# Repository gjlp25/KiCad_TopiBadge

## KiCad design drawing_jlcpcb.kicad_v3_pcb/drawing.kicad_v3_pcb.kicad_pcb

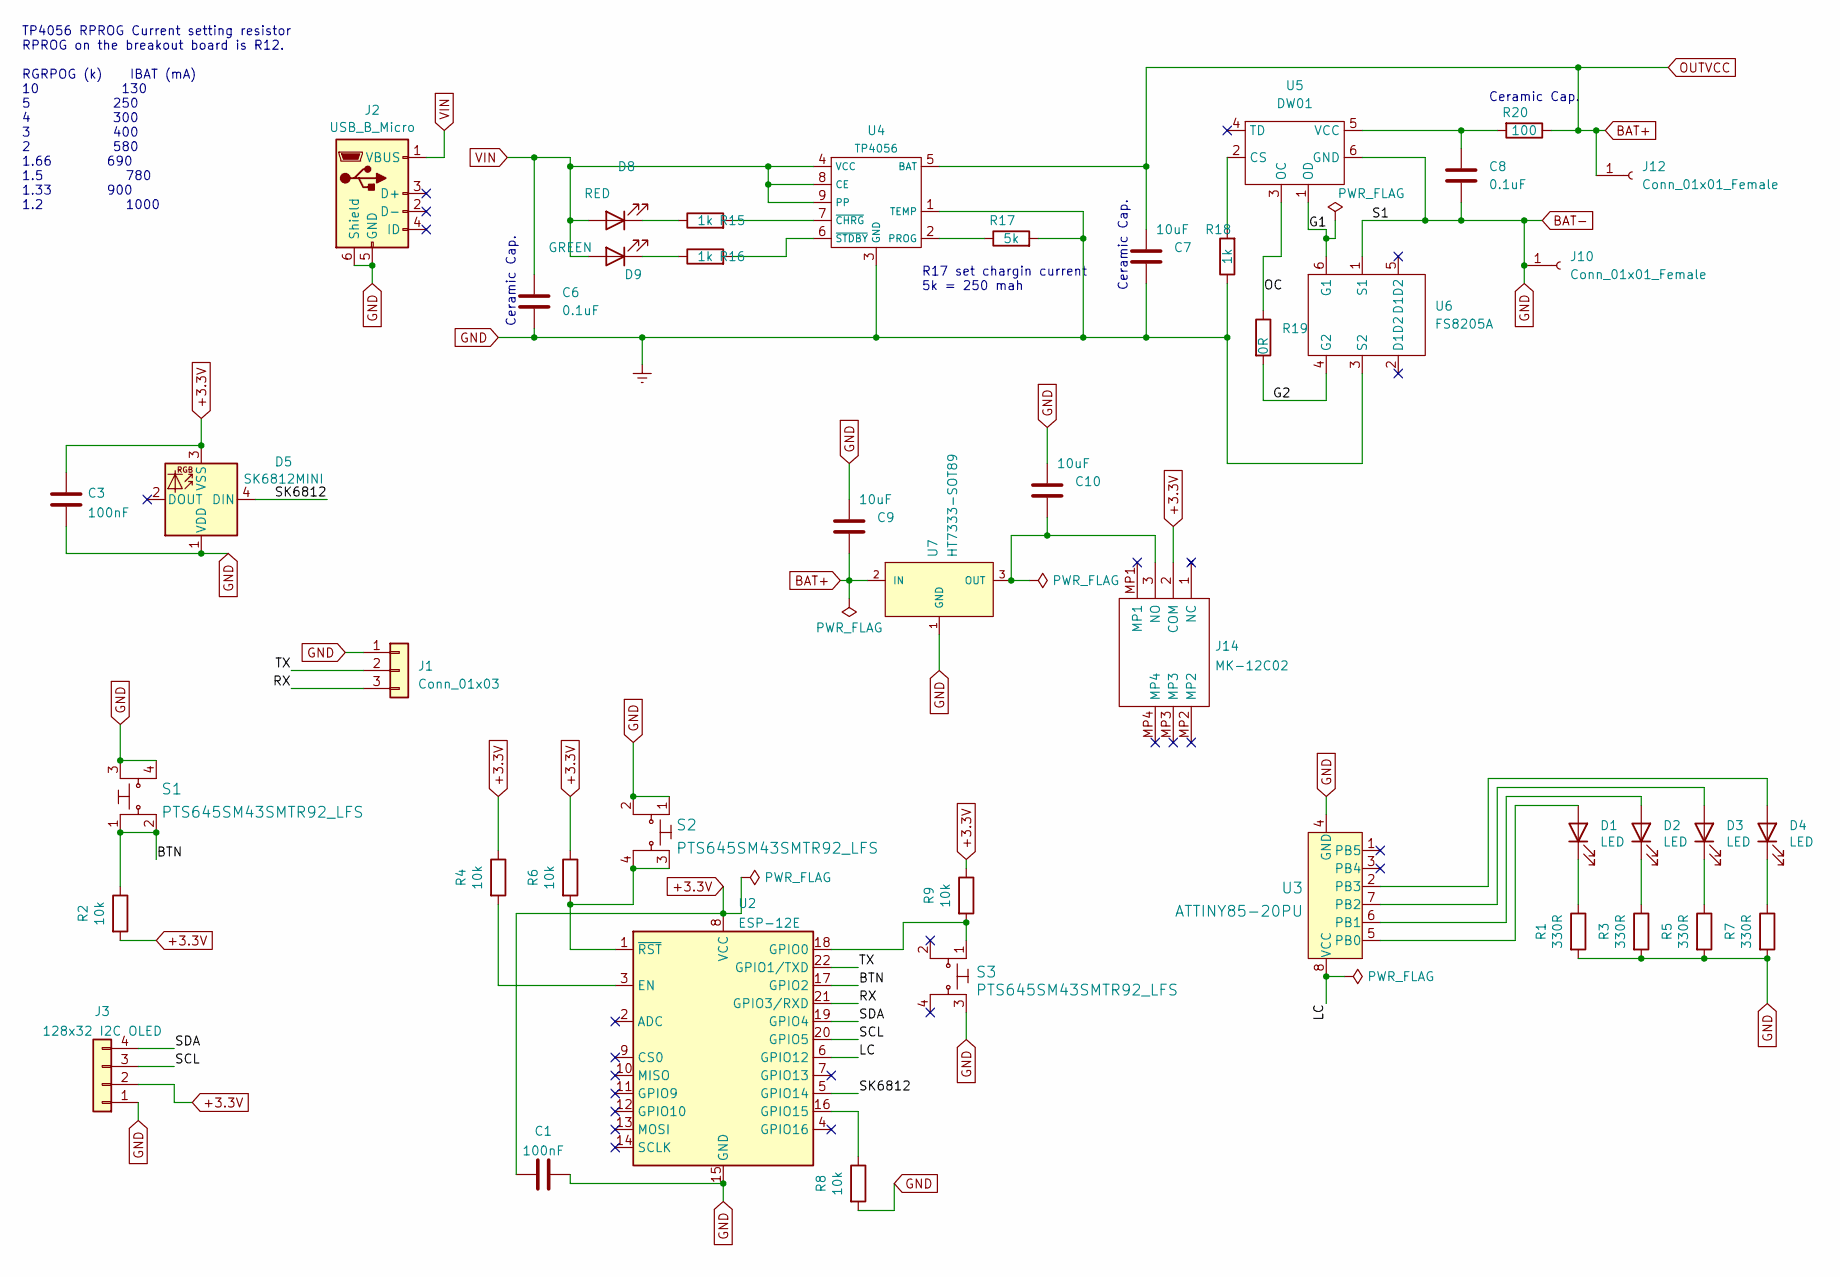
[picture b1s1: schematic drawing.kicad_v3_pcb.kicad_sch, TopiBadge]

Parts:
C1, C3: 100nF; C_0805_2012Metric_Pad1.18x1.45mm_HandSolder
C6, C8: 0.1uF; C_0805_2012Metric_Pad1.18x1.45mm_HandSolder
C7, C9, C10: 10uF; C_0805_2012Metric_Pad1.18x1.45mm_HandSolder
D1, D2, D3, D4: LED; LED_0805_2012Metric_Pad1.15x1.40mm_HandSolder
D5: SK6812MINI; LED_SK6812MINI_PLCC4_3.5x3.5mm_P1.75mm
D8: RED; LED_0805_2012Metric_Pad1.15x1.40mm_HandSolder
D9: GREEN; LED_0805_2012Metric_Pad1.15x1.40mm_HandSolder
J1: Conn_01x03; PinSocket_1x03_P2.54mm_Horizontal
J2: USB_B_Micro; USB_Micro_B_Female_10118194-0001LF
J3: 128x32 I2C OLED; PinSocket_1x04_P2.54mm_Vertical
J10, J12: Conn_01x01_Female; solderpad
J14: MK-12C02; MK12C02; Manufacturer_Part_Number MK-12C02
R1, R3, R5, R7: 330R; R_0805_2012Metric_Pad1.20x1.40mm_HandSolder
R2, R4, R6, R8, R9: 10k; R_0805_2012Metric_Pad1.20x1.40mm_HandSolder
R15, R16, R18: 1k; R_0603_1608Metric_Pad0.98x0.95mm_HandSolder
R17: 5k; R_0805_2012Metric_Pad1.20x1.40mm_HandSolder
R19: 0R; R_1206_3216Metric_Pad1.30x1.75mm_HandSolder
R20: 100; R_0805_2012Metric_Pad1.20x1.40mm_HandSolder
S1, S2, S3: PTS645SM43SMTR92_LFS; Switch_Tactile_SMD_6x6mm_PTS645; MPN PTS645SM43SMTR92 LFS; Digi-Key_PN CKN9112CT-ND
U2: ESP-12E
U3: ATTINY85-20PU; SMDIP-8_W7.62mm; MPN ATTINY85-20PU; Digi-Key_PN ATTINY85-20PU-ND
U4: TP4056; SOIC-8-1EP_3.9x4.9mm_P1.27mm_EP2.29x3mm
U5: DW01; SOT-23-6_Handsoldering
U6: FS8205A; SOT-23-6_Handsoldering
U7: HT7333-SOT89; Holtek-HT7333-SOT89-Level_A

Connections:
+3.3V: C1.1, C3.2, D5.3 (VSS), J3.2, J14.2 (COM), R2.2, R4.1, R6.1, R9.1, U2.8 (VCC)
/BTN: R2.1, S1.1, S1.2, U2.17 (GPIO2)
/G1: U5.1 (OD), U6.6 (G1)
/G2: R19.2, U6.4 (G2)
/LC: U2.6 (GPIO12), U3.8 (VCC)
/OC: R19.1, U5.3 (OC)
/RX: J1.3, U2.21 (GPIO3/RXD)
/SCL: J3.3, U2.20 (GPIO5)
/SDA: J3.4, U2.19 (GPIO4)
/SK6812: D5.4 (DIN), U2.5 (GPIO14)
/TX: J1.2, U2.22 (GPIO1/TXD)
BAT+: C7.1, C9.2, J12.1, R20.1, U4.5 (BAT), U7.2 (IN)
BAT-: C1.2, C3.1, C6.2, C7.2, C8.2, C9.1, C10.1, D5.1 (VDD), J1.1, J2.5 (GND), J2.6 (Shield), J3.1, J10.1, R1.2, R3.2, R5.2, R7.2, R8.2, R17.2, R18.1, S1.3, S1.4, S2.1, S2.2, S3.3, U2.15 (GND), U3.4 (GND), U4.1 (TEMP), U4.3 (GND), U5.6 (GND), U6.1 (S1), U6.3 (S2), U7.1 (GND)
unnamed: D1.2 (A), U3.5 (PB0)
unnamed: D1.1 (K), R1.1
unnamed: D2.2 (A), U3.6 (PB1)
unnamed: D2.1 (K), R3.1
unnamed: D3.2 (A), U3.7 (PB2)
unnamed: D3.1 (K), R5.1
unnamed: D4.2 (A), U3.2 (PB3)
unnamed: D4.1 (K), R7.1
unnamed: D8.1 (K), R15.1
unnamed: D9.1 (K), R16.1
unnamed: C10.2, J14.3 (NO), U7.3 (OUT)
unnamed: R4.2, U2.3 (EN)
unnamed: R9.2, S3.1, U2.18 (GPIO0)
unnamed: R8.1, U2.16 (GPIO15)
unnamed: R6.2, S2.3, S2.4, U2.1 (~RST)
unnamed: R17.1, U4.2 (PROG)
unnamed: R15.2, U4.7 (~CHRG)
unnamed: R16.2, U4.6 (~STDBY)
unnamed: R18.2, U5.2 (CS)
unnamed: C8.1, R20.2, U5.5 (VCC)
VIN: C6.1, D8.2 (A), D9.2 (A), J2.1 (VBUS), U4.4 (VCC), U4.8 (CE), U4.9 (PP)

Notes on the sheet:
Ceramic Cap.
TP4056 RPROG Current setting resistor RPROG on the breakout board is R12. RGRPOG (k) IBAT (mA) 10 130 5 250 4 300 3 400 2 580 1.66 690 1.5 780 1.33 900 1.2 1000
R17 set chargin current 5k = 250 mah

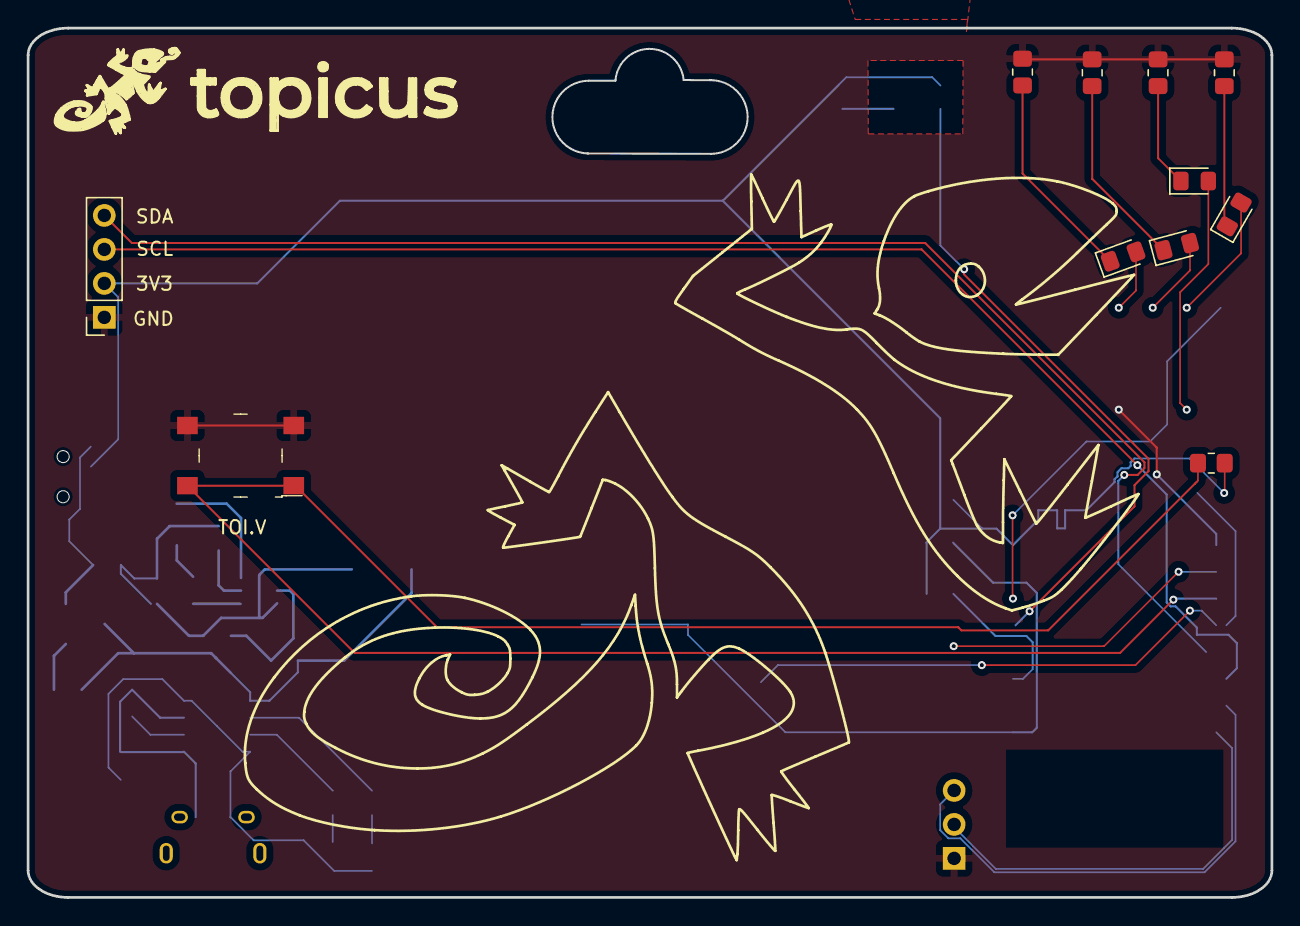
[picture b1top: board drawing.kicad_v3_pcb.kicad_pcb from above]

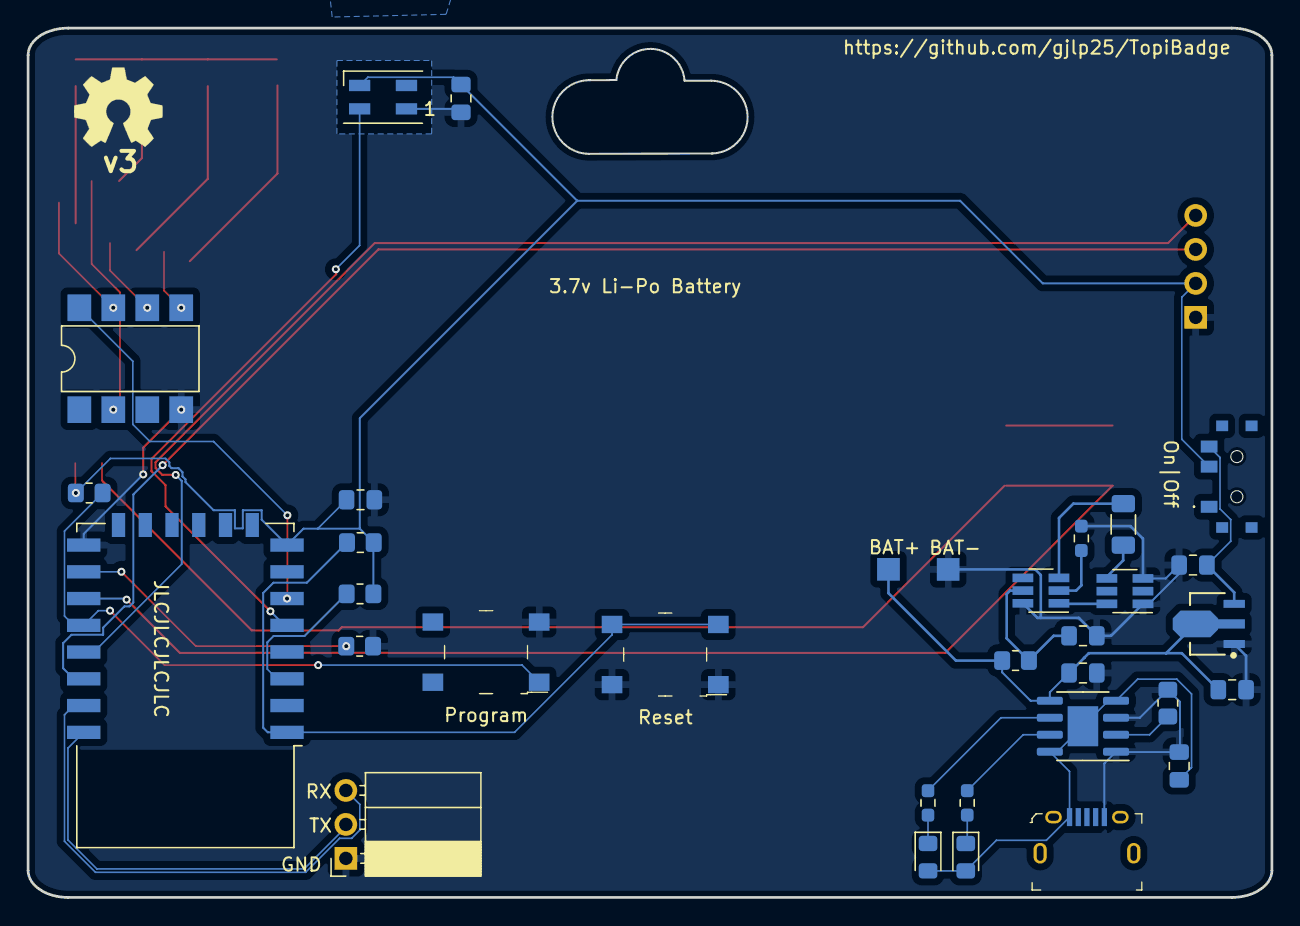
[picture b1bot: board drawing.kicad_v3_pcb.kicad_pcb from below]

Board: 4 copper layers, 93.0 x 65.0 mm, 44 parts (33 on the bottom side), 34 nets.

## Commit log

2022-02-16 Addes KiCad files for the project
2022-02-16 Added KiCad files for the project
2022-05-10 Layout fixes in v2.2
2022-05-10 Silkscreen cleanup in v3.0
2022-05-11 Updated charging circuit
2022-05-18 Fixed charging circuit in v3.0
2022-05-21 Fixed esp8266 programming circuit in v3.0
2022-05-30 Run from 18650 and fixed HT7333 circuit
2024-07-08 Fixed HT7333 and charging circuit
2024-07-08 Deleted corrupt files
2024-07-08 Deleted irrelevant files
2024-07-08 Changed TH components to SMD
2024-07-09 Added 3d models to renders
2024-07-13 Added board for pcbway
2024-07-21 added yellow soldermask

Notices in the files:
drawing_jlcpcb.kicad_v3_pcb/drawing.kicad_v3_pcb.kicad_pcb:
creativecommons.org/licenses/by/4.0
License: CC BY 4.0
